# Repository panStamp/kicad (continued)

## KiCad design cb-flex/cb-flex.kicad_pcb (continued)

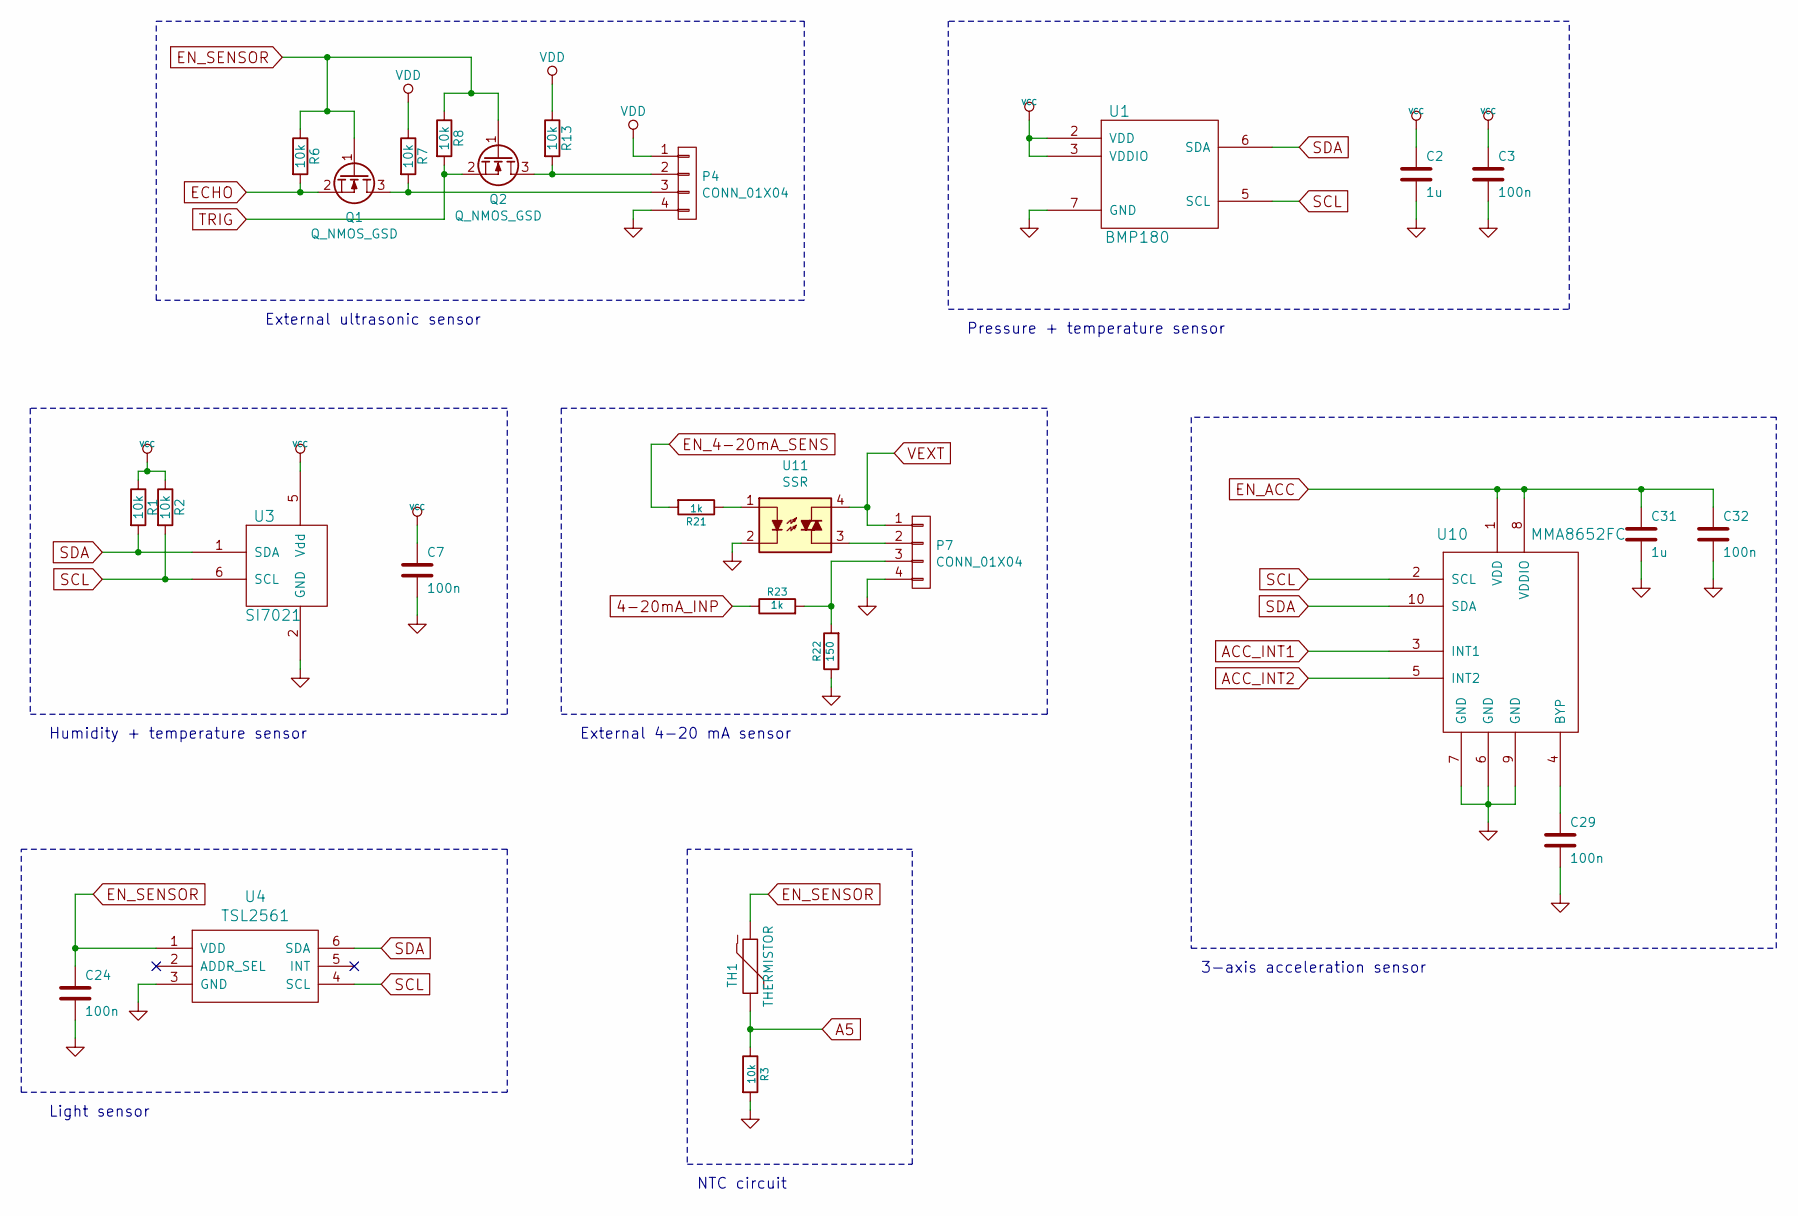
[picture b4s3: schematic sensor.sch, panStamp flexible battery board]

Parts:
C2, C31: 1u; SM0603S
C3, C7, C24, C29, C32: 100n; SM0603S
P4, P7: CONN_01X04; Pin_Header_Straight_1x04
Q1, Q2: Q_NMOS_GSD; SOT23
R1, R2, R3, R6, R7, R8, R13: 10k; SM0603S
R21, R23: 1k; SM0603S
R22: 150; SM0603S
TH1: THERMISTOR; SM0603S
U1: BMP180
U3: SI7021; DFN-6
U4: TSL2561; DFN-6
U10: MMA8652FC; DFN-10
U11: SSR; SMT-DIP-4

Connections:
4-20mA_INP: R23.1; also elsewhere on the board
A5: R3.1, TH1.1; also elsewhere on the board
ACC_INT1: U10.3 (INT1); also elsewhere on the board
ACC_INT2: U10.5 (INT2); also elsewhere on the board
ECHO: Q1.2 (S), R6.2; also elsewhere on the board
EN_4-20mA_SENS: R21.2; also elsewhere on the board
EN_ACC: C31.1, C32.1, U10.1 (VDD), U10.8 (VDDIO); also elsewhere on the board
EN_SENSOR: C24.1, Q1.1 (G), Q2.1 (G), R6.1, R8.1, TH1.2, U4.1 (VDD); also elsewhere on the board
GND: C2.2, C3.2, C7.2, C24.2, C29.2, C31.2, C32.2, P4.4, P7.4, R3.2, R22.1, U1.7 (GND), U3.2 (GND), U4.3 (GND), U10.6 (GND), U10.7 (GND), U10.9 (GND), U11.2; also elsewhere on the board
unnamed: C29.1, U10.4 (BYP)
unnamed: P4.2, Q2.3 (D), R13.2
unnamed: P4.3, Q1.3 (D), R7.2
unnamed: P7.2, U11.3
unnamed: P7.3, R22.2, R23.2
unnamed: R21.1, U11.1
SCL: R2.2, U1.5 (SCL), U3.6 (SCL), U4.4 (SCL), U10.2 (SCL); also elsewhere on the board
SDA: R1.2, U1.6 (SDA), U3.1 (SDA), U4.6 (SDA), U10.10 (SDA); also elsewhere on the board
TRIG: Q2.2 (S), R8.2; also elsewhere on the board
VCC: C2.1, C3.1, C7.1, R1.1, R2.1, U1.2 (VDD), U1.3 (VDDIO), U3.5 (Vdd); also elsewhere on the board
VDD: P4.1, R7.1, R13.1; also elsewhere on the board
VEXT: P7.1, U11.4; also elsewhere on the board

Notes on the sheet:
External ultrasonic sensor
Pressure + temperature sensor
Humidity + temperature sensor
NTC circuit
Light sensor
3-axis acceleration sensor
External 4-20 mA sensor

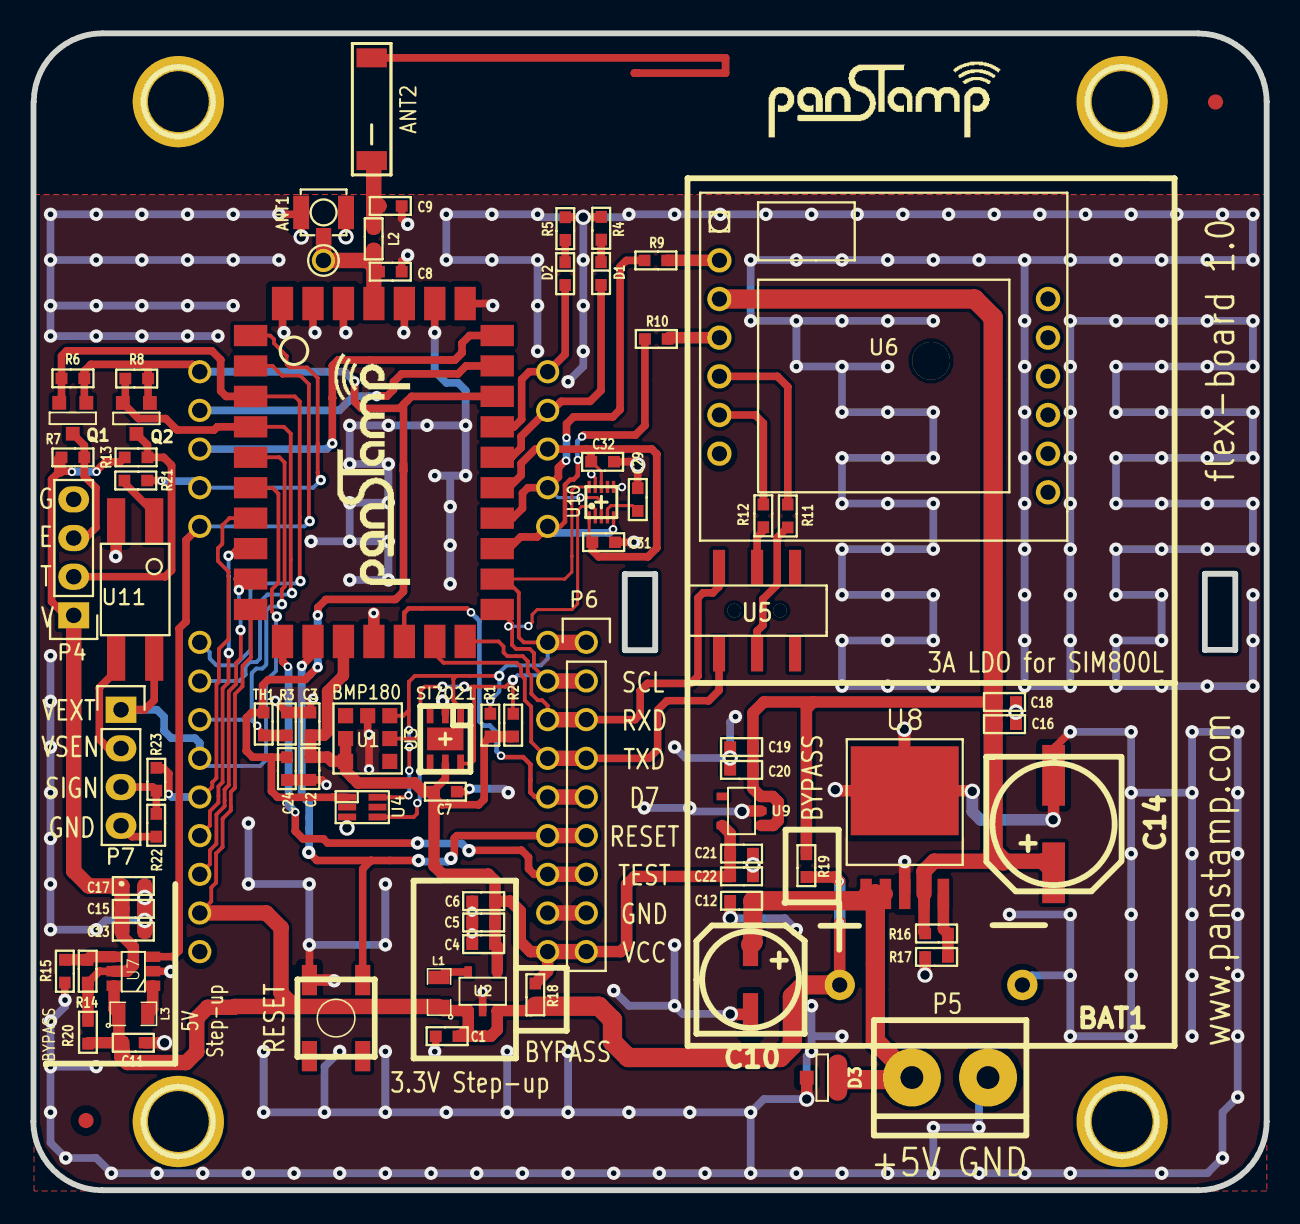
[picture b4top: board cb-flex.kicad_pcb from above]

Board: 4 copper layers, 81.0 x 76.0 mm, 87 parts (0 on the bottom side), 50 nets.

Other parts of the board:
1PIN, 1PIN#2, 1PIN#3, 1PIN#4: P***; 1pin
fiducial: VAL**; fiducial
fiducial#2: VAL**; fiducial

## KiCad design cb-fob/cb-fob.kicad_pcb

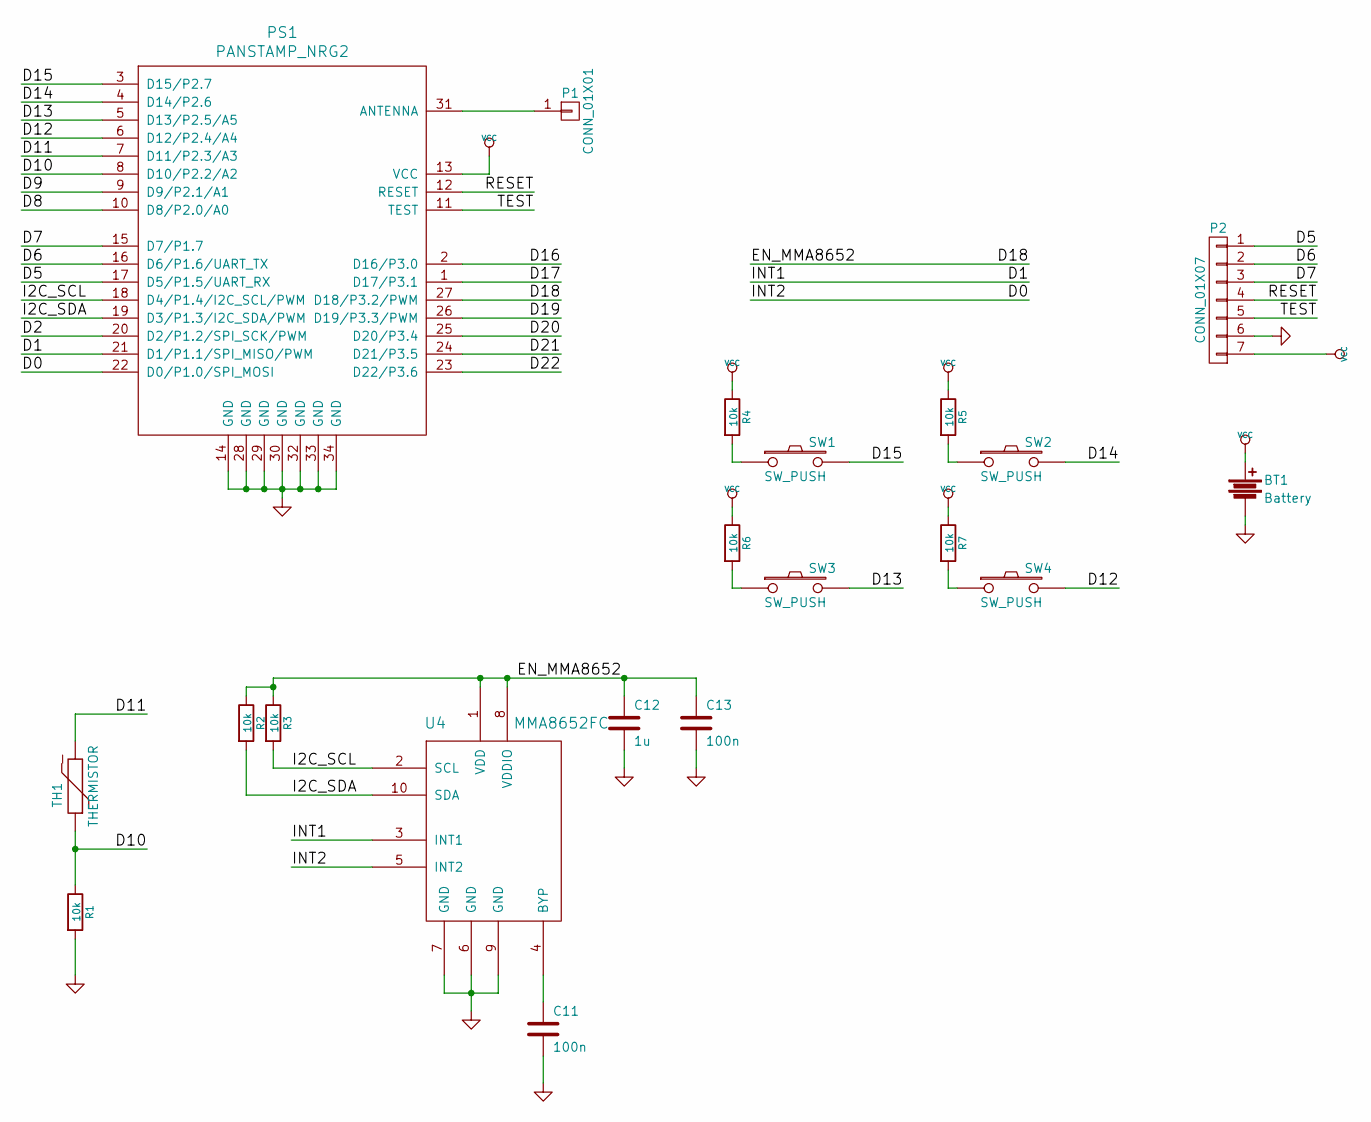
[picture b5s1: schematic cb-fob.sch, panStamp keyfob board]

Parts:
BT1: Battery; linx_bat-hld-001
C11, C13: 100n; SM0603S
C12: 1u; SM0603S
P1: CONN_01X01; Pin_Header_Straight_1x01
P2: CONN_01X07; Pin_Header_Straight_1x07
PS1: PANSTAMP_NRG2; PANSTAMP_2
R1, R2, R3, R4, R5, R6, R7: 10k; SM0603S
SW1, SW2, SW3, SW4: SW_PUSH; SW_SPST_B3SL-1002P
TH1: THERMISTOR; SM0603S
U4: MMA8652FC; DFN-10

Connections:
/D0: PS1.22 (D0/P1.0/SPI_MOSI), U4.5 (INT2)
/D1: PS1.21 (D1/P1.1/SPI_MISO/PWM), U4.3 (INT1)
/D2: PS1.20 (D2/P1.2/SPI_SCK/PWM)
/D5: P2.1, PS1.17 (D5/P1.5/UART_RX)
/D6: P2.2, PS1.16 (D6/P1.6/UART_TX)
/D7: P2.3, PS1.15 (D7/P1.7)
/D8: PS1.10 (D8/P2.0/A0)
/D9: PS1.9 (D9/P2.1/A1)
/D10: PS1.8 (D10/P2.2/A2), R1.1, TH1.1
/D11: PS1.7 (D11/P2.3/A3), TH1.2
/D12: PS1.6 (D12/P2.4/A4), SW4.2
/D13: PS1.5 (D13/P2.5/A5), SW3.2
/D14: PS1.4 (D14/P2.6), SW2.2
/D15: PS1.3 (D15/P2.7), SW1.2
/D16: PS1.2 (D16/P3.0)
/D17: PS1.1 (D17/P3.1)
/D18: C12.1, C13.1, PS1.27 (D18/P3.2/PWM), R2.1, R3.1, U4.1 (VDD), U4.8 (VDDIO)
/D19: PS1.26 (D19/P3.3/PWM)
/D20: PS1.25 (D20/P3.4)
/D21: PS1.24 (D21/P3.5)
/D22: PS1.23 (D22/P3.6)
/I2C_SCL: PS1.18 (D4/P1.4/I2C_SCL/PWM), R3.2, U4.2 (SCL)
/I2C_SDA: PS1.19 (D3/P1.3/I2C_SDA/PWM), R2.2, U4.10 (SDA)
/RESET: P2.4, PS1.12 (RESET)
/TEST: P2.5, PS1.11 (TEST)
GND: BT1.2, C11.2, C12.2, C13.2, P2.6, PS1.14 (GND), PS1.28 (GND), PS1.29 (GND), PS1.30 (GND), PS1.32 (GND), PS1.33 (GND), PS1.34 (GND), R1.2, U4.6 (GND), U4.7 (GND), U4.9 (GND)
unnamed: C11.1, U4.4 (BYP)
unnamed: P1.1, PS1.31 (ANTENNA)
unnamed: R4.2, SW1.1
unnamed: R5.2, SW2.1
unnamed: R6.2, SW3.1
unnamed: R7.2, SW4.1
VCC: BT1.1, P2.7, PS1.13 (VCC), R4.1, R5.1, R6.1, R7.1

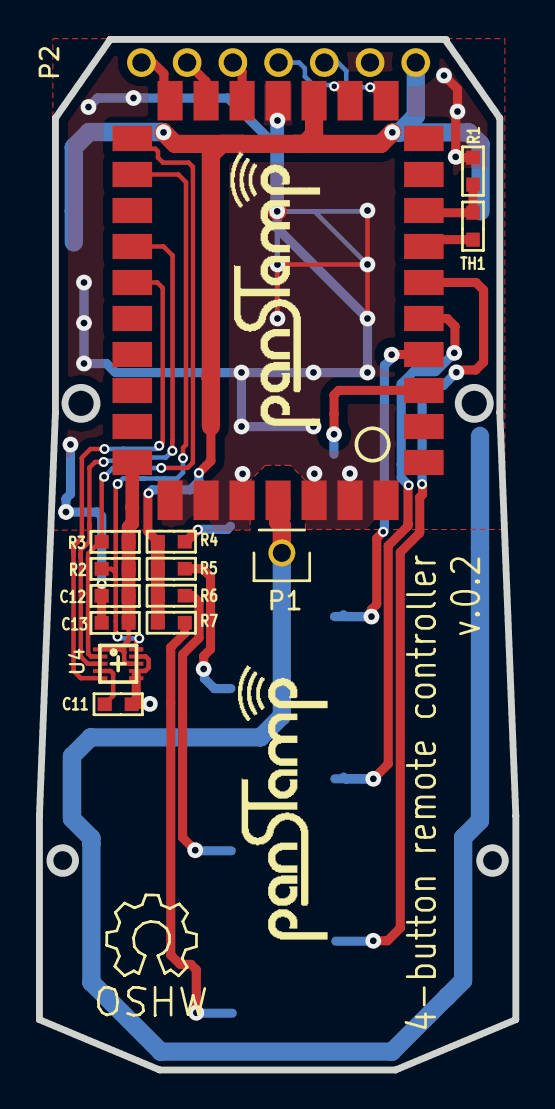
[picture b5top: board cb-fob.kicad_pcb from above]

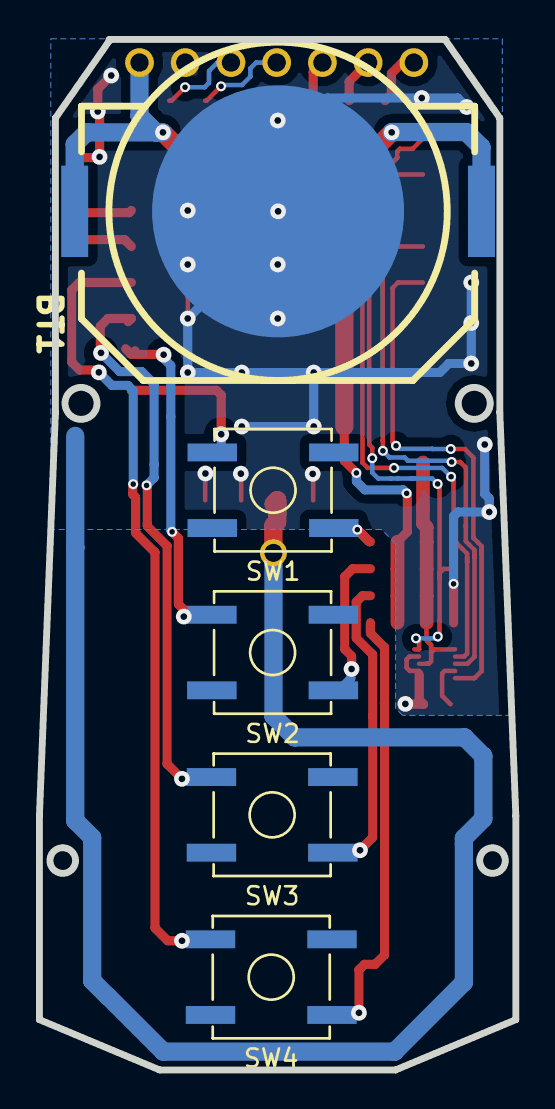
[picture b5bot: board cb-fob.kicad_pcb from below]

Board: 4 copper layers, 26.5 x 57.3 mm, 20 parts (5 on the bottom side), 24 nets.

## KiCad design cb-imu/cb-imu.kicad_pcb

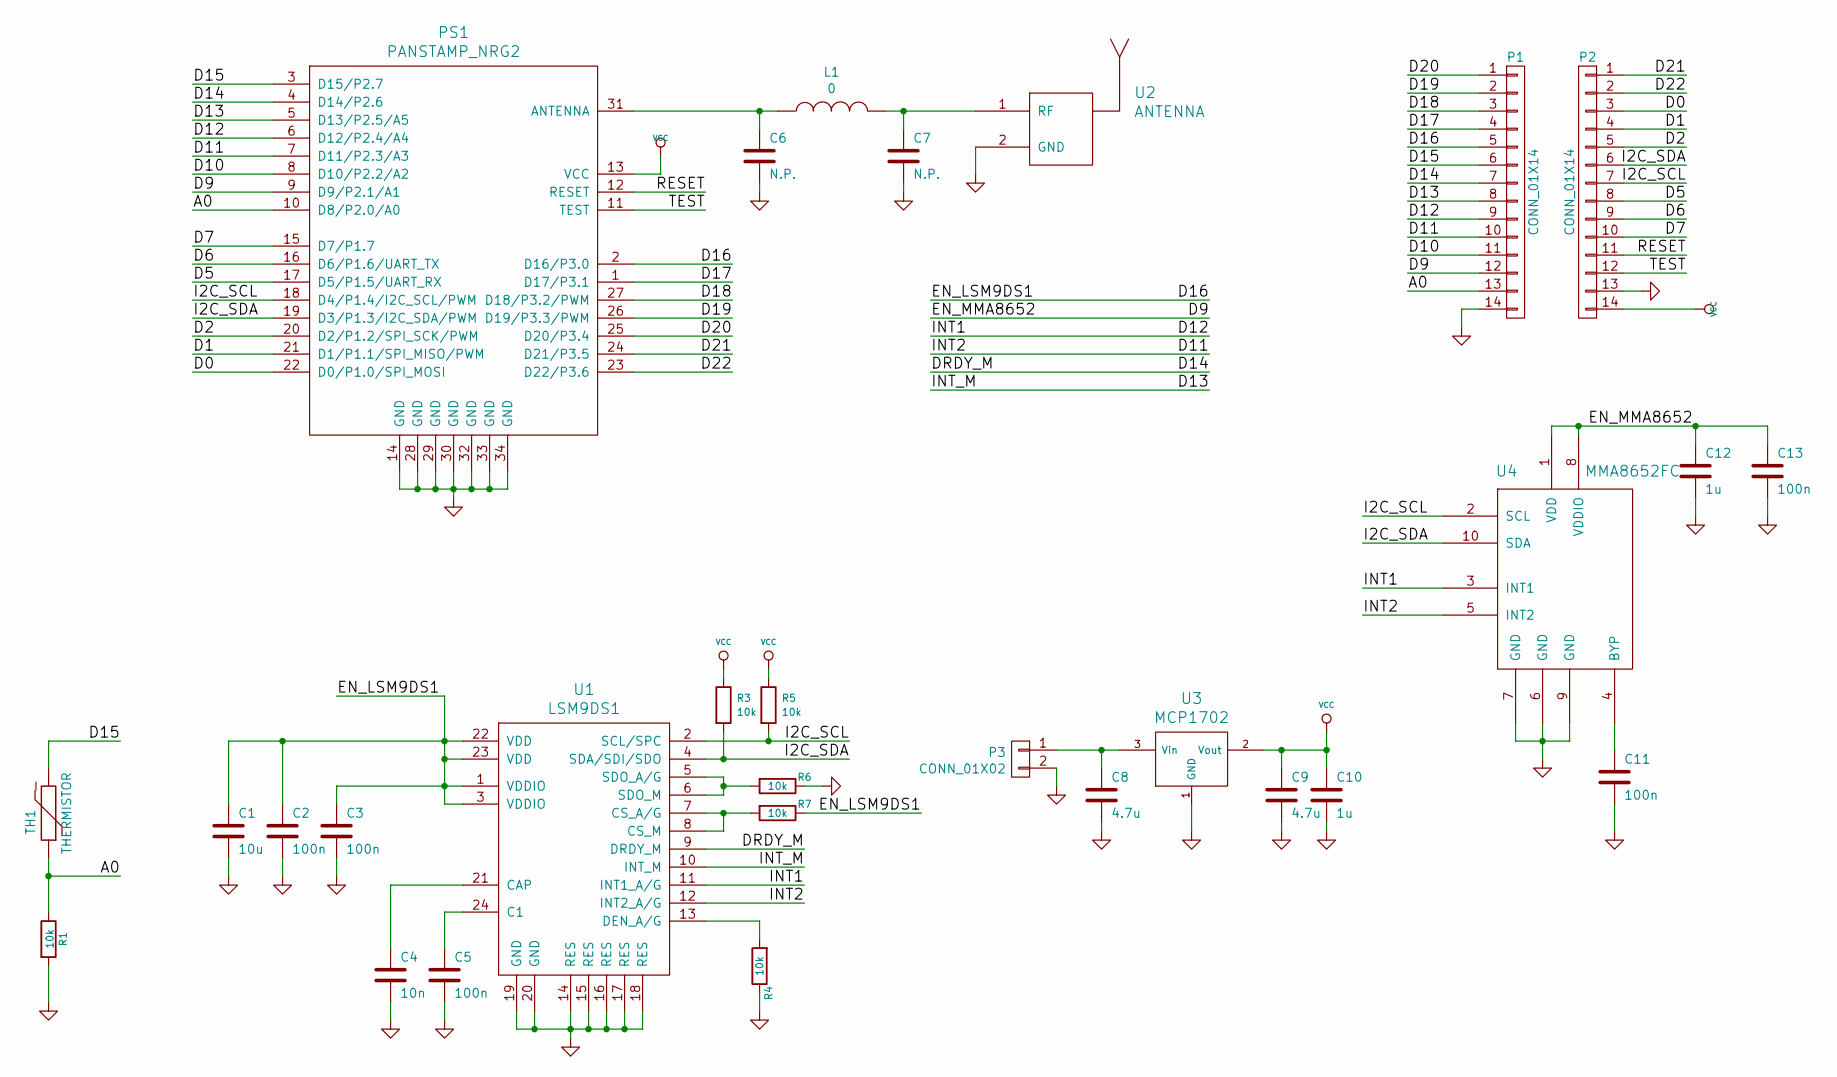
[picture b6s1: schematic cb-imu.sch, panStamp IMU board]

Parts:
C1: 10u; SM0603S
C2, C3, C5, C11, C13: 100n; SM0603S
C4: 10n; SM0603S
C6, C7: N.P.; SM0603S
C8, C9: 4.7u; SM0603S
C10, C12: 1u; SM0603S
L1: 0; SM0603S
P1, P2: CONN_01X14; Pin_Header_Straight_1x12
P3: CONN_01X02; Pin_Header_Straight_1x02
PS1: PANSTAMP_NRG2; PANSTAMP_2
R1, R3, R4, R5, R6, R7: 10k; SM0603S
TH1: THERMISTOR; SM0603S
U1: LSM9DS1; LGA24L
U2: ANTENNA; U.FL_CONN
U3: MCP1702; SOT23
U4: MMA8652FC; DFN-10

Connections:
/A0: P1.13, PS1.10 (D8/P2.0/A0), R1.1, TH1.1
/D0: P2.3, PS1.22 (D0/P1.0/SPI_MOSI)
/D1: P2.4, PS1.21 (D1/P1.1/SPI_MISO/PWM)
/D2: P2.5, PS1.20 (D2/P1.2/SPI_SCK/PWM)
/D5: P2.8, PS1.17 (D5/P1.5/UART_RX)
/D6: P2.9, PS1.16 (D6/P1.6/UART_TX)
/D7: P2.10, PS1.15 (D7/P1.7)
/D9: C12.1, C13.1, P1.12, PS1.9 (D9/P2.1/A1), U4.1 (VDD), U4.8 (VDDIO)
/D10: P1.11, PS1.8 (D10/P2.2/A2)
/D11: P1.10, PS1.7 (D11/P2.3/A3), U1.12 (INT2_A/G), U4.5 (INT2)
/D12: P1.9, PS1.6 (D12/P2.4/A4), U1.11 (INT1_A/G), U4.3 (INT1)
/D13: P1.8, PS1.5 (D13/P2.5/A5), U1.10 (INT_M)
/D14: P1.7, PS1.4 (D14/P2.6), U1.9 (DRDY_M)
/D15: P1.6, PS1.3 (D15/P2.7), TH1.2
/D16: C1.1, C2.1, C3.1, P1.5, PS1.2 (D16/P3.0), R7.1, U1.1 (VDDIO), U1.3 (VDDIO), U1.22 (VDD), U1.23 (VDD)
/D17: P1.4, PS1.1 (D17/P3.1)
/D18: P1.3, PS1.27 (D18/P3.2/PWM)
/D19: P1.2, PS1.26 (D19/P3.3/PWM)
/D20: P1.1, PS1.25 (D20/P3.4)
/D21: P2.1, PS1.24 (D21/P3.5)
/D22: P2.2, PS1.23 (D22/P3.6)
/I2C_SCL: P2.7, PS1.18 (D4/P1.4/I2C_SCL/PWM), R5.2, U1.2 (SCL/SPC), U4.2 (SCL)
/I2C_SDA: P2.6, PS1.19 (D3/P1.3/I2C_SDA/PWM), R3.2, U1.4 (SDA/SDI/SDO), U4.10 (SDA)
/RESET: P2.11, PS1.12 (RESET)
/TEST: P2.12, PS1.11 (TEST)
GND: C1.2, C2.2, C3.2, C4.2, C5.2, C6.2, C7.2, C8.2, C9.2, C10.2, C11.2, C12.2, C13.2, P1.14, P2.13, P3.2, PS1.14 (GND), PS1.28 (GND), PS1.29 (GND), PS1.30 (GND), PS1.32 (GND), PS1.33 (GND), PS1.34 (GND), R1.2, R4.1, R6.1, U1.14 (RES), U1.15 (RES), U1.16 (RES), U1.17 (RES), U1.18 (RES), U1.19 (GND), U1.20 (GND), U2.2 (GND), U3.1 (GND), U4.6 (GND), U4.7 (GND), U4.9 (GND)
unnamed: C4.1, U1.21 (CAP)
unnamed: C5.1, U1.24 (C1)
unnamed: C6.1, L1.1, PS1.31 (ANTENNA)
unnamed: C7.1, L1.2, U2.1 (RF)
unnamed: C8.1, P3.1, U3.3 (Vin)
unnamed: C11.1, U4.4 (BYP)
unnamed: R4.2, U1.13 (DEN_A/G)
unnamed: R6.2, U1.5 (SDO_A/G), U1.6 (SDO_M)
unnamed: R7.2, U1.7 (CS_A/G), U1.8 (CS_M)
VCC: C9.1, C10.1, P2.14, PS1.13 (VCC), R3.1, R5.1, U3.2 (Vout)

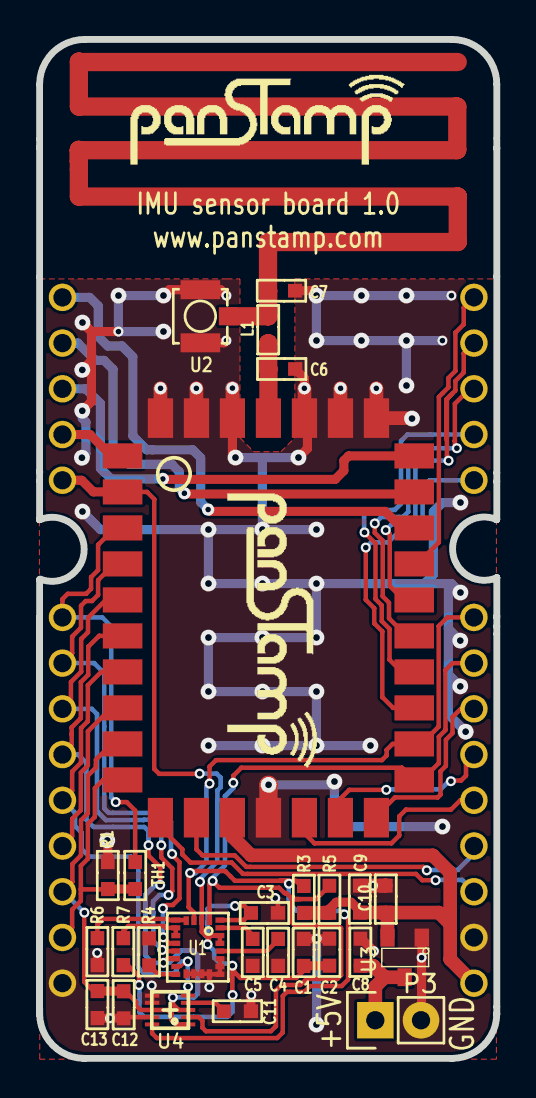
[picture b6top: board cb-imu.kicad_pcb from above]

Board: 4 copper layers, 25.4 x 56.6 mm, 29 parts (0 on the bottom side), 36 nets.

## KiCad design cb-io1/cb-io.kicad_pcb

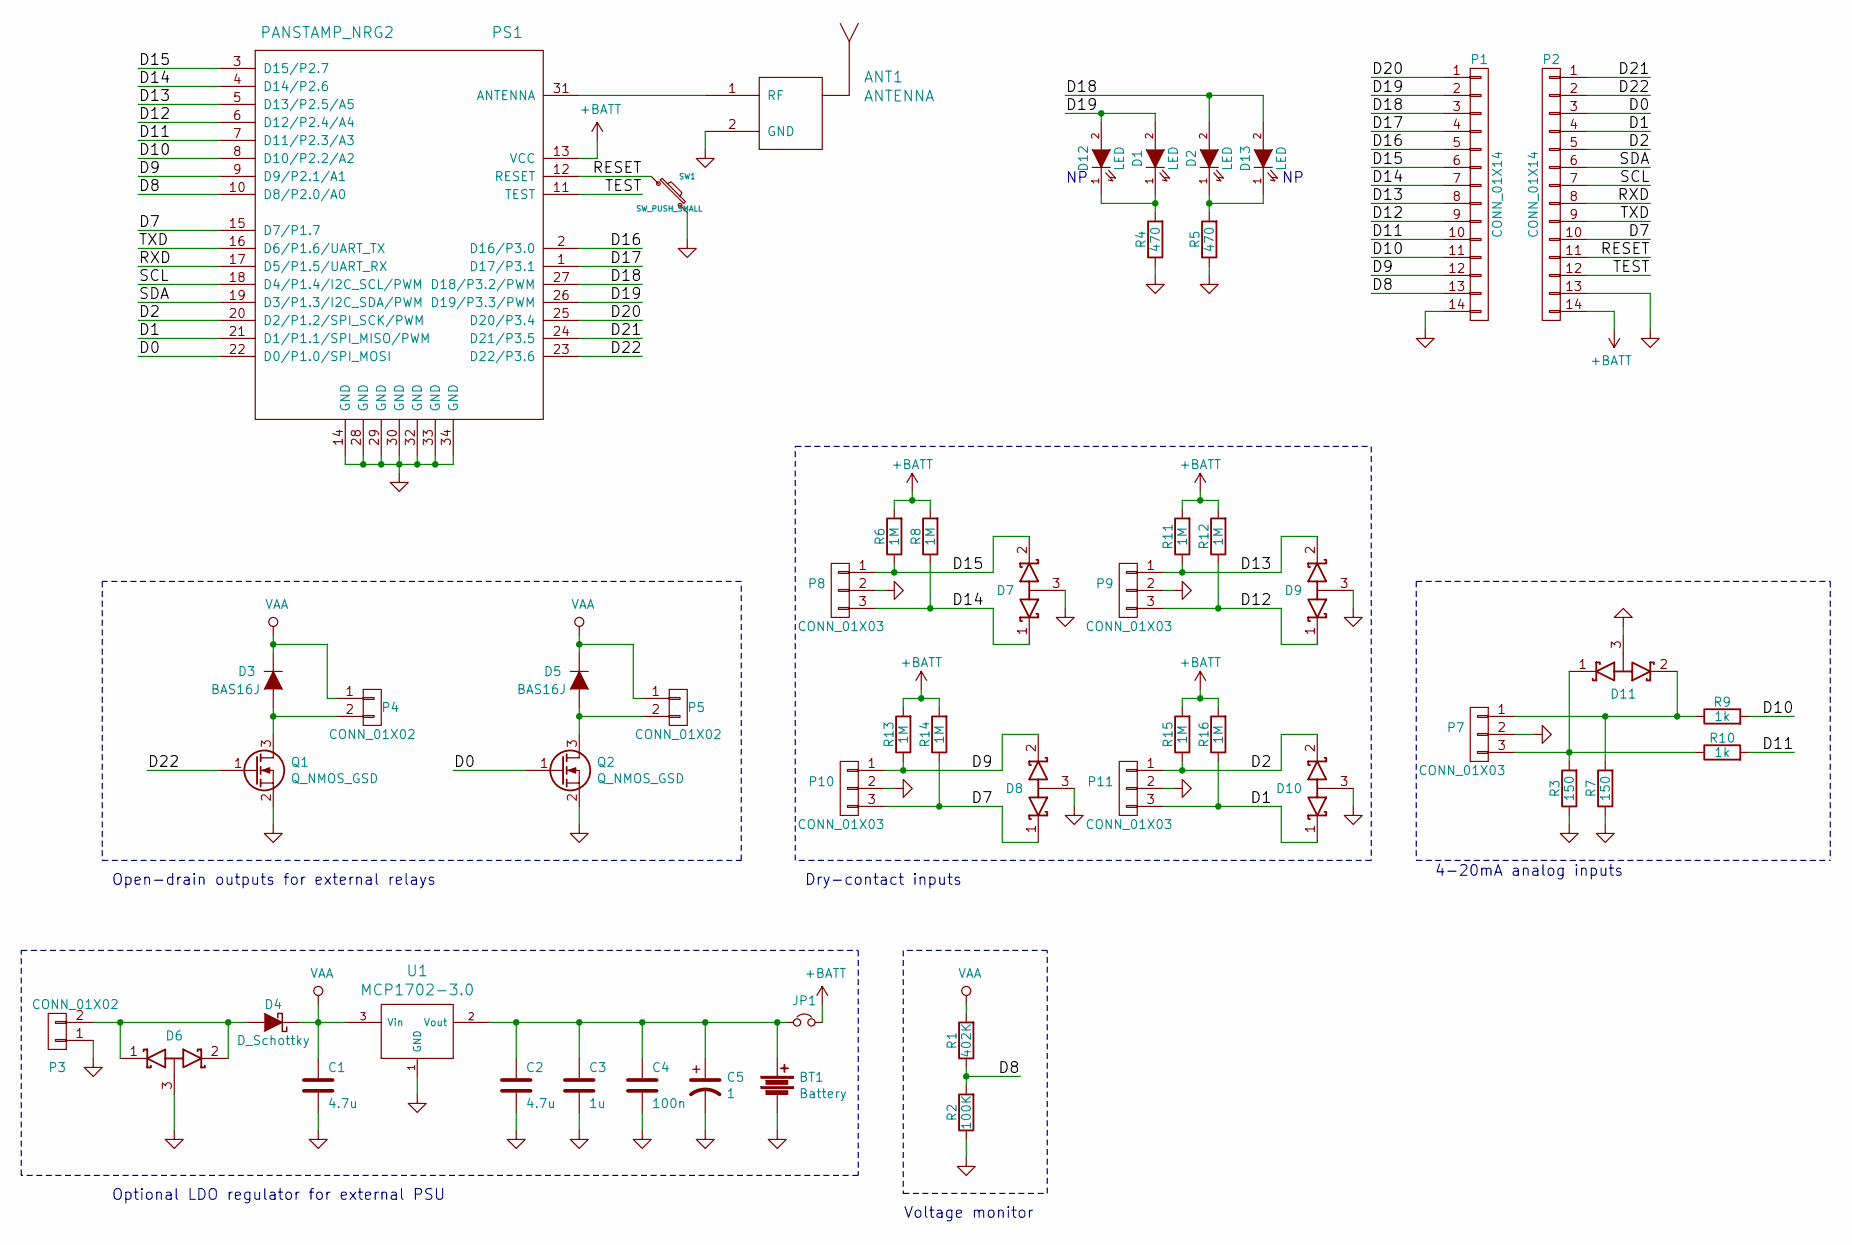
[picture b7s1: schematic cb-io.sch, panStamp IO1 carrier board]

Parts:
ANT1: ANTENNA; SMA_RightAngle_Tyco
BT1: Battery; BAT_AA_HOLDER_02
C1, C2: 4.7u; SM0603S
C3: 1u; SM0603S
C4: 100n; SM0603S
C5: 1; SUPERCAP_1F_5V
D1, D2: LED; SM0603S_POL
D3, D5: BAS16J; SOD323
D4: D_Schottky; SMA
D6, D7, D8, D9, D10, D11: D_Schottky_x2_ACom_KKA; SOT23
D12, D13: LED; Pin_Header_Straight_1x02
JP1: Jumper_NC_Small; Pin_Header_Straight_1x02
P1, P2: CONN_01X14; Pin_Header_Straight_1x12
P3, P4, P5: CONN_01X02; terminal_block_3.5mm_2P
P7, P8, P9, P10, P11: CONN_01X03; terminal_block_3.5mm_3P
PS1: PANSTAMP_NRG2; PANSTAMP_2
Q1, Q2: Q_NMOS_GSD; SOT23
R1: 402K; SM0603S
R2: 100K; SM0603S
R3, R7: 150; SM0603S
R4, R5: 470; SM0603S
R6, R8, R11, R12, R13, R14, R15, R16: 1M; SM0603S
R9, R10: 1k; SM0603S
SW1: SW_PUSH_SMALL; switch-tact-noah
U1: MCP1702-3.0; SOT23

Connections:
+BATT: JP1.2, P2.14, PS1.13 (VCC), R6.2, R8.2, R11.2, R12.2, R13.2, R14.2, R15.2, R16.2
/D0: P2.3, PS1.22 (D0/P1.0/SPI_MOSI), Q2.1 (G)
/D1: D10.1 (K), P2.4, P11.3, PS1.21 (D1/P1.1/SPI_MISO/PWM), R16.1
/D2: D10.2 (K), P2.5, P11.1, PS1.20 (D2/P1.2/SPI_SCK/PWM), R15.1
/D7: D8.1 (K), P2.10, P10.3, PS1.15 (D7/P1.7), R14.1
/D8: P1.13, PS1.10 (D8/P2.0/A0), R1.1, R2.2
/D9: D8.2 (K), P1.12, P10.1, PS1.9 (D9/P2.1/A1), R13.1
/D10: P1.11, PS1.8 (D10/P2.2/A2), R9.2
/D11: P1.10, PS1.7 (D11/P2.3/A3), R10.2
/D12: D9.1 (K), P1.9, P9.3, PS1.6 (D12/P2.4/A4), R12.1
/D13: D9.2 (K), P1.8, P9.1, PS1.5 (D13/P2.5/A5), R11.1
/D14: D7.1 (K), P1.7, P8.3, PS1.4 (D14/P2.6), R8.1
/D15: D7.2 (K), P1.6, P8.1, PS1.3 (D15/P2.7), R6.1
/D16: P1.5, PS1.2 (D16/P3.0)
/D17: P1.4, PS1.1 (D17/P3.1)
/D18: D2.2 (A), D13.2 (A), P1.3, PS1.27 (D18/P3.2/PWM)
/D19: D1.2 (A), D12.2 (A), P1.2, PS1.26 (D19/P3.3/PWM)
/D20: P1.1, PS1.25 (D20/P3.4)
/D21: P2.1, PS1.24 (D21/P3.5)
/D22: P2.2, PS1.23 (D22/P3.6), Q1.1 (G)
/RESET: P2.11, PS1.12 (RESET), SW1.1
/RXD: P2.8, PS1.17 (D5/P1.5/UART_RX)
/SCL: P2.7, PS1.18 (D4/P1.4/I2C_SCL/PWM)
/SDA: P2.6, PS1.19 (D3/P1.3/I2C_SDA/PWM)
/TEST: P2.12, PS1.11 (TEST)
/TXD: P2.9, PS1.16 (D6/P1.6/UART_TX)
GND: ANT1.2 (GND), BT1.2, C1.2, C2.2, C3.2, C4.2, C5.2, D6.3 (A), D7.3 (A), D8.3 (A), D9.3 (A), D10.3 (A), D11.3 (A), P1.14, P2.13, P3.1, P7.2, P8.2, P9.2, P10.2, P11.2, PS1.14 (GND), PS1.28 (GND), PS1.29 (GND), PS1.30 (GND), PS1.32 (GND), PS1.33 (GND), PS1.34 (GND), Q1.2 (S), Q2.2 (S), R2.1, R3.1, R4.1, R5.1, R7.1, SW1.2, U1.1 (GND)
unnamed: ANT1.1 (RF), PS1.31 (ANTENNA)
unnamed: BT1.1, C2.1, C3.1, C4.1, C5.1, JP1.1, U1.2 (Vout)
unnamed: D1.1 (K), D12.1 (K), R4.2
unnamed: D3.2 (A), P4.2, Q1.3 (D)
unnamed: D4.2 (A), D6.1 (K), D6.2 (K), P3.2
unnamed: D5.2 (A), P5.2, Q2.3 (D)
unnamed: D11.1 (K), P7.3, R3.2, R10.1
unnamed: D11.2 (K), P7.1, R7.2, R9.1
unnamed: D2.1 (K), D13.1 (K), R5.2
VAA: C1.1, D3.1 (K), D4.1 (K), D5.1 (K), P4.1, P5.1, R1.2, U1.3 (Vin)

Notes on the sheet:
Optional LDO regulator for external PSU
Open-drain outputs for external relays
Dry-contact inputs
Voltage monitor
4-20mA analog inputs

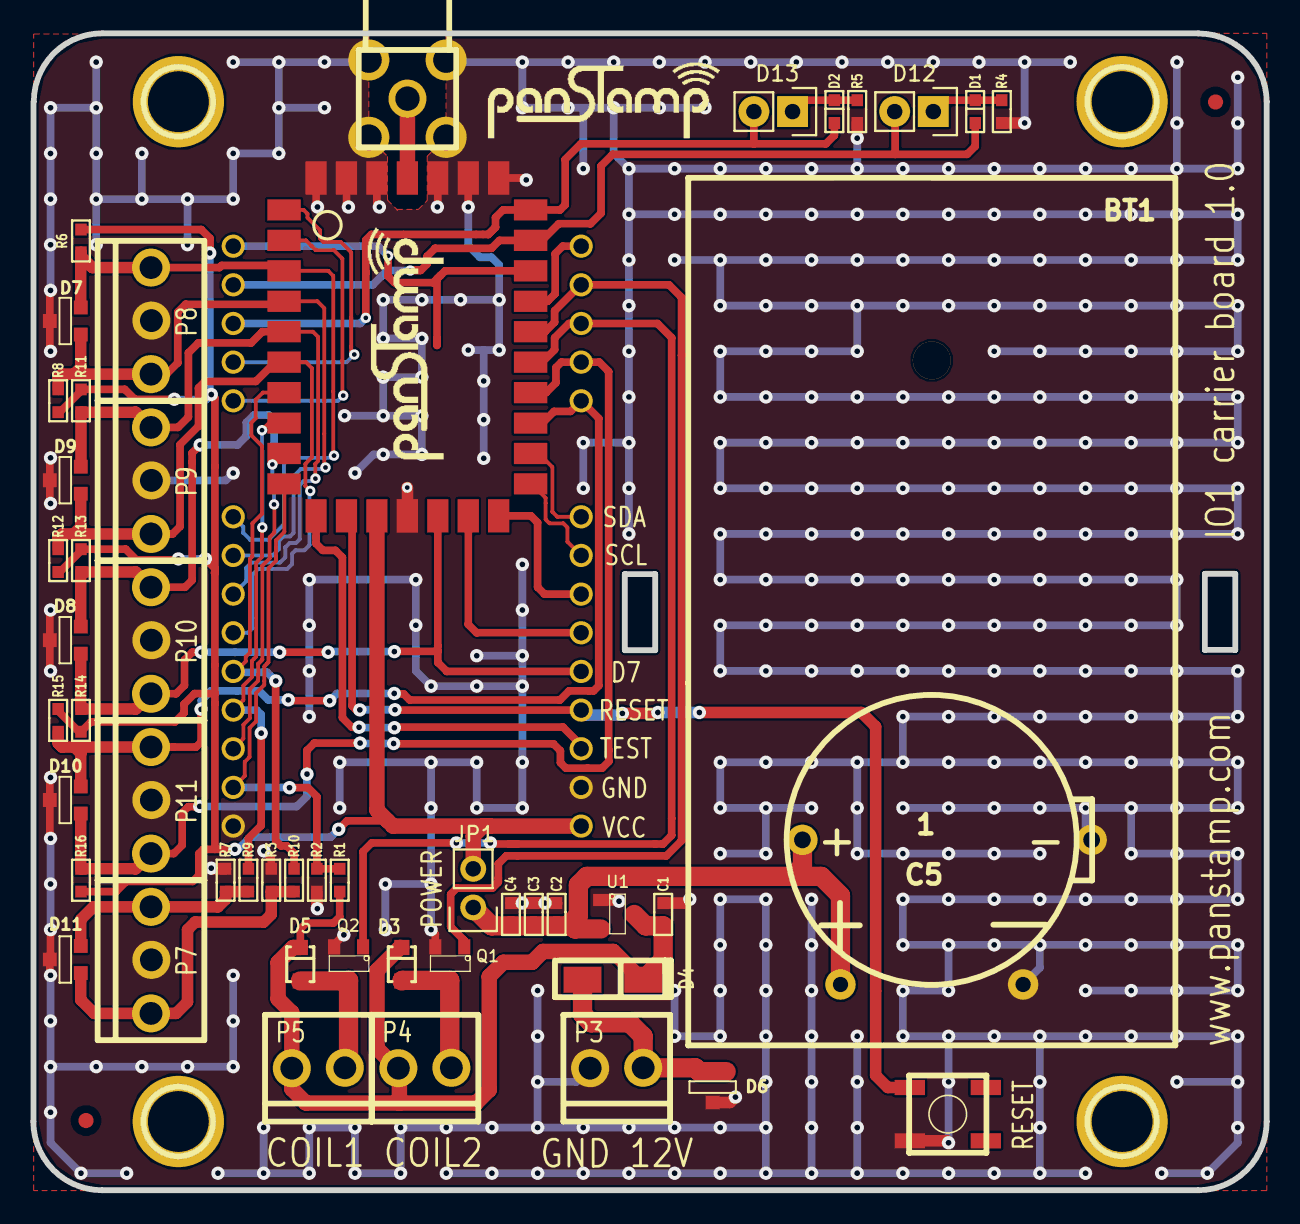
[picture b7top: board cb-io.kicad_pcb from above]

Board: 4 copper layers, 81.0 x 76.0 mm, 58 parts (0 on the bottom side), 37 nets.

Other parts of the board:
1PIN, 1PIN#2, 1PIN#3, 1PIN#4: P***; 1pin
fiducial: VAL**; fiducial
fiducial#2: VAL**; fiducial

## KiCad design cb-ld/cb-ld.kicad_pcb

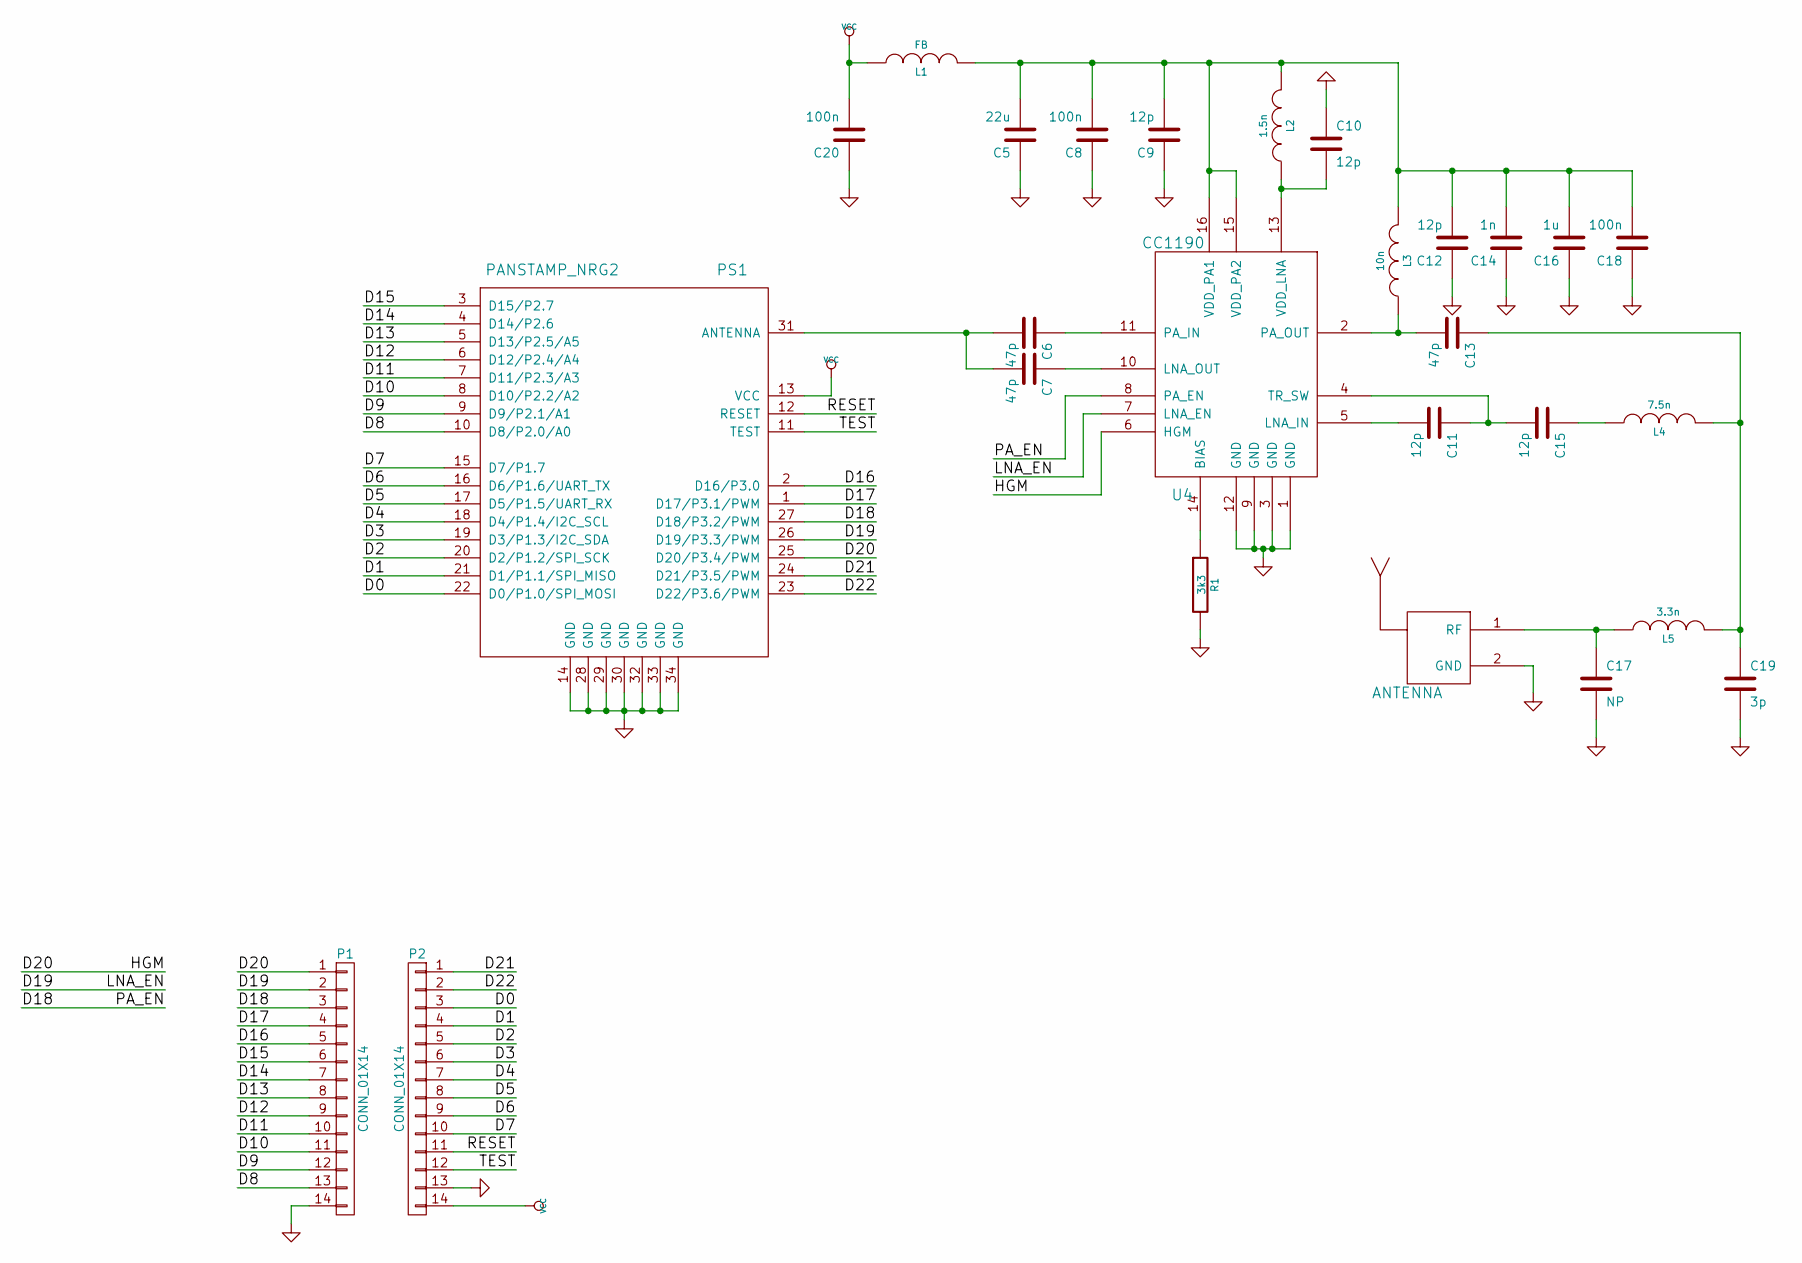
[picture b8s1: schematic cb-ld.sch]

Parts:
ANT1: ANTENNA; SMD_SMA_RP
C5: 22u; SM0805
C6, C7, C13: 47p; SM0603S
C8, C18, C20: 100n; SM0603S
C9, C10, C11, C12, C15: 12p; SM0603S
C14: 1n; SM0603S
C16: 1u; SM0603S
C17: NP; SM0603S
C19: 3p; SM0603S
L1: FB; SM0603S
L2: 1.5n; SM0603S
L3: 10n; SM0603S
L4: 7.5n; SM0603S
L5: 3.3n; SM0603S
P1, P2: CONN_01X14; Pin_Header_Straight_1x12
PS1: PANSTAMP_NRG2; PANSTAMP_2
R1: 3k3; SM0603S
U4: CC1190; VQFN16

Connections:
/D0: P2.3, PS1.22 (D0/P1.0/SPI_MOSI)
/D1: P2.4, PS1.21 (D1/P1.1/SPI_MISO)
/D2: P2.5, PS1.20 (D2/P1.2/SPI_SCK)
/D3: P2.6, PS1.19 (D3/P1.3/I2C_SDA)
/D4: P2.7, PS1.18 (D4/P1.4/I2C_SCL)
/D5: P2.8, PS1.17 (D5/P1.5/UART_RX)
/D6: P2.9, PS1.16 (D6/P1.6/UART_TX)
/D7: P2.10, PS1.15 (D7/P1.7)
/D8: P1.13, PS1.10 (D8/P2.0/A0)
/D9: P1.12, PS1.9 (D9/P2.1/A1)
/D10: P1.11, PS1.8 (D10/P2.2/A2)
/D11: P1.10, PS1.7 (D11/P2.3/A3)
/D12: P1.9, PS1.6 (D12/P2.4/A4)
/D13: P1.8, PS1.5 (D13/P2.5/A5)
/D14: P1.7, PS1.4 (D14/P2.6)
/D15: P1.6, PS1.3 (D15/P2.7)
/D16: P1.5, PS1.2 (D16/P3.0)
/D17: P1.4, PS1.1 (D17/P3.1/PWM)
/D18: P1.3, PS1.27 (D18/P3.2/PWM), U4.8 (PA_EN)
/D19: P1.2, PS1.26 (D19/P3.3/PWM), U4.7 (LNA_EN)
/D20: P1.1, PS1.25 (D20/P3.4/PWM), U4.6 (HGM)
/D21: P2.1, PS1.24 (D21/P3.5/PWM)
/D22: P2.2, PS1.23 (D22/P3.6/PWM)
/RESET: P2.11, PS1.12 (RESET)
/TEST: P2.12, PS1.11 (TEST)
GND: ANT1.2 (GND), C5.1, C8.1, C9.1, C10.1, C12.1, C14.1, C16.1, C17.2, C18.1, C19.2, C20.1, P1.14, P2.13, PS1.14 (GND), PS1.28 (GND), PS1.29 (GND), PS1.30 (GND), PS1.32 (GND), PS1.33 (GND), PS1.34 (GND), R1.2, U4.1 (GND), U4.3 (GND), U4.9 (GND), U4.12 (GND), U4.17
unnamed: ANT1.1 (RF), C17.1, L5.1
unnamed: C6.1, U4.11 (PA_IN)
unnamed: C6.2, C7.2, PS1.31 (ANTENNA)
unnamed: C7.1, U4.10 (LNA_OUT)
unnamed: C10.2, L2.1, U4.13 (VDD_LNA)
unnamed: C11.1, C15.2, U4.4 (TR_SW)
unnamed: C11.2, U4.5 (LNA_IN)
unnamed: C5.2, C8.2, C9.2, C12.2, C14.2, C16.2, C18.2, L1.2, L2.2, L3.2, U4.15 (VDD_PA2), U4.16 (VDD_PA1)
unnamed: C13.1, C19.1, L4.2, L5.2
unnamed: C13.2, L3.1, U4.2 (PA_OUT)
unnamed: C15.1, L4.1
unnamed: R1.1, U4.14 (BIAS)
VCC: C20.2, L1.1, P2.14, PS1.13 (VCC)

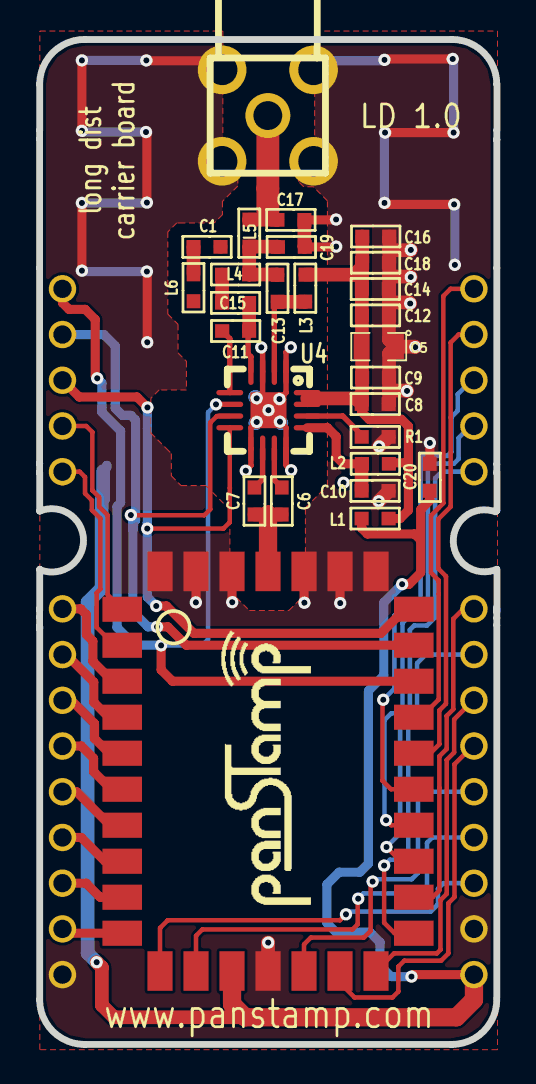
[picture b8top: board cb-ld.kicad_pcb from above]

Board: 4 copper layers, 25.4 x 55.8 mm, 29 parts (0 on the bottom side), 40 nets.

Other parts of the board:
C1: 47p; SM0603S
L6: 6.8n; SM0603S

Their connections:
unnamed: C1.1, L6.1
